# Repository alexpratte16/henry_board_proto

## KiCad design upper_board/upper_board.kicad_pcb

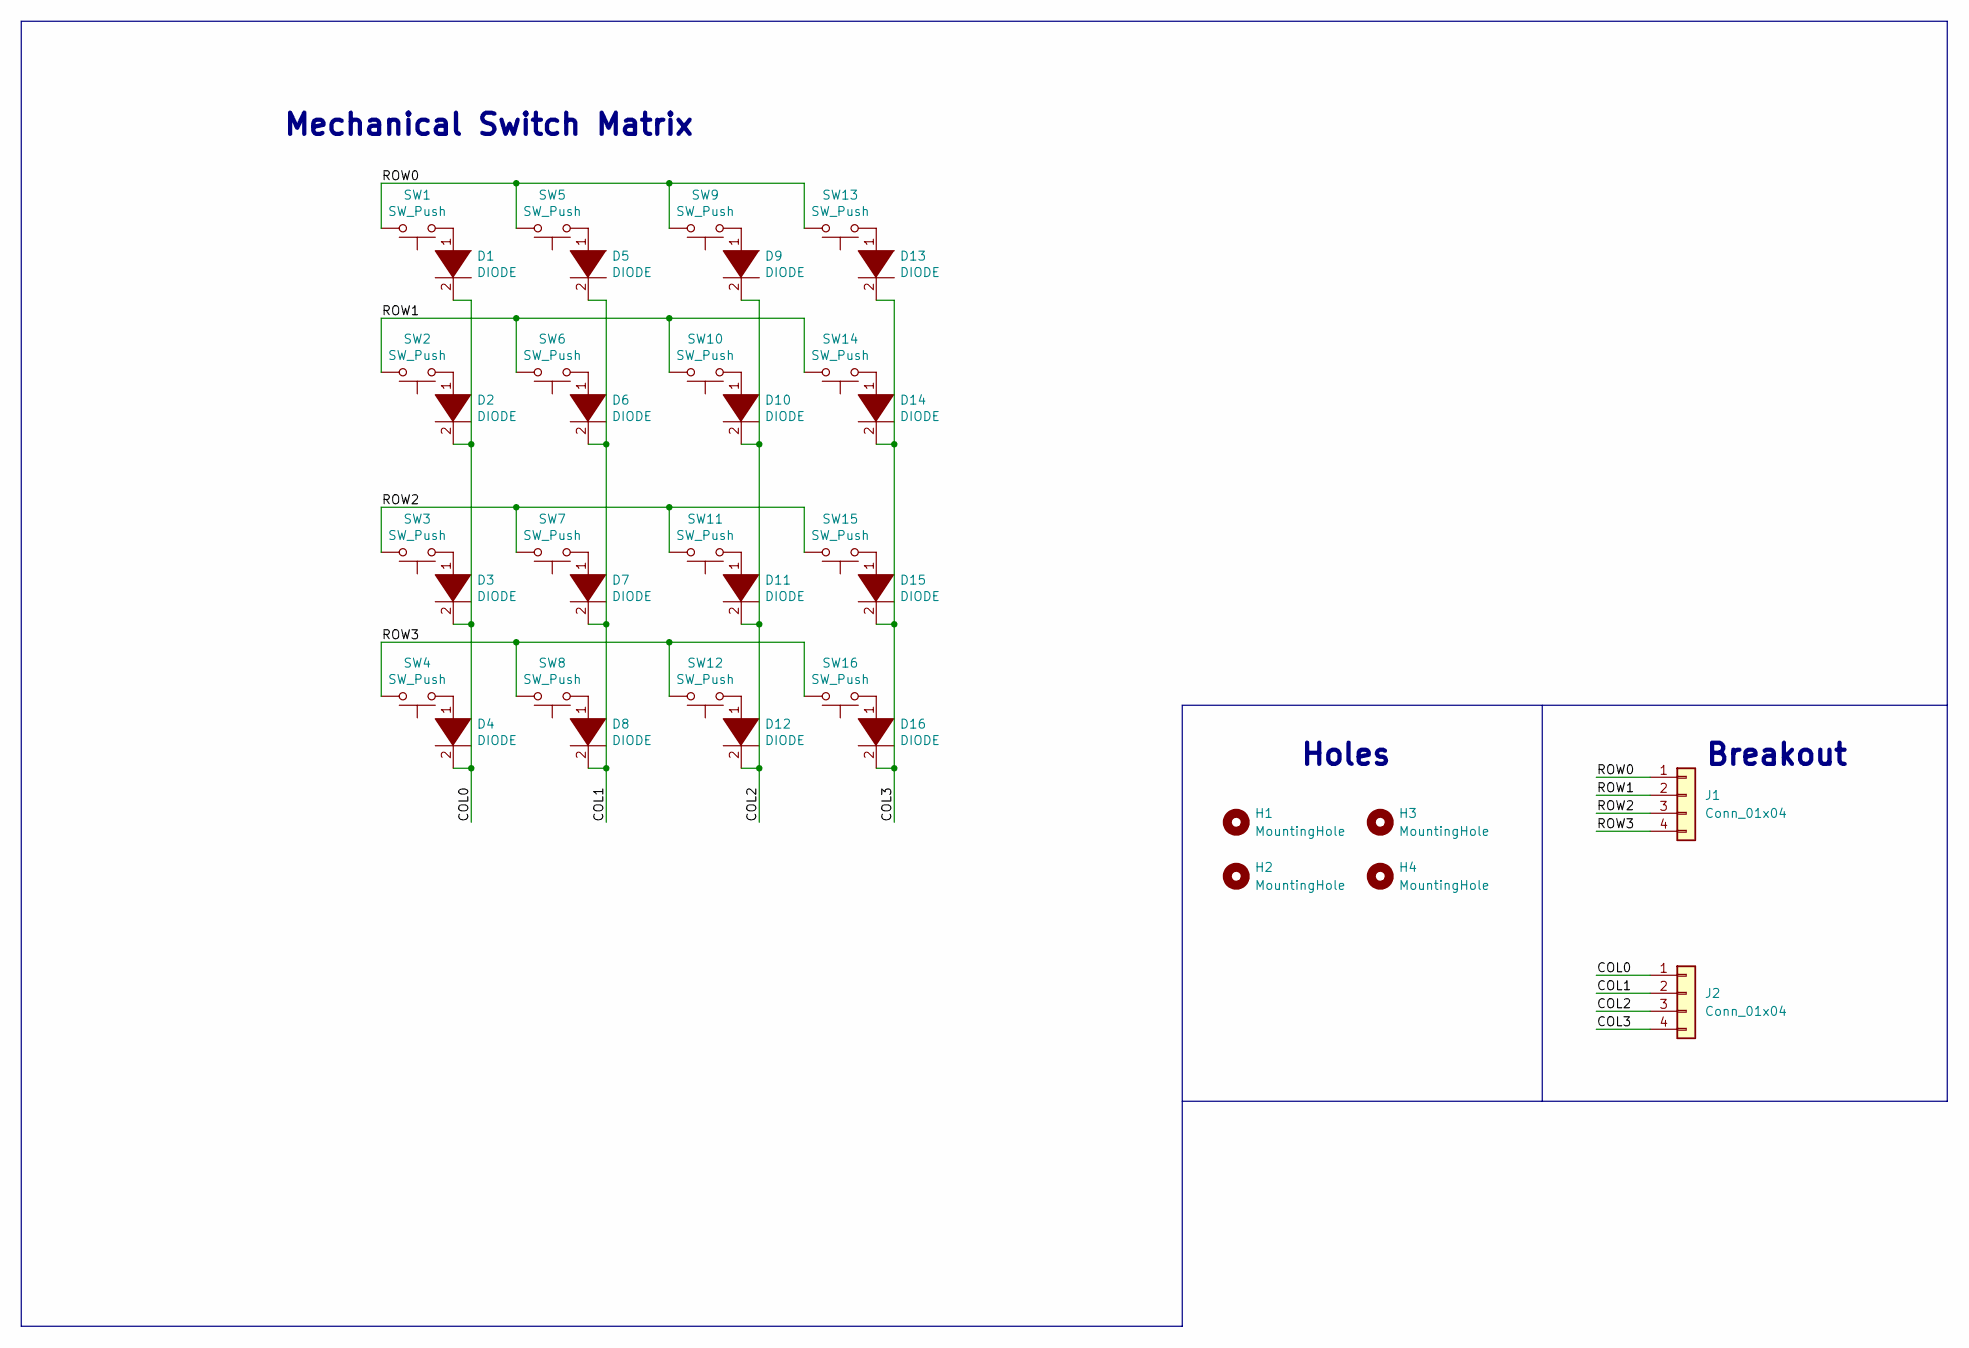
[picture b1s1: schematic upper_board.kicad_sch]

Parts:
D1, D2, D3, D4, D5, D6, D7, D8, D9, D10, D11, D12, D13, D14, D15, D16: DIODE; D_1206_3216Metric
H1, H2, H3, H4: MountingHole; MountingHole_2.5mm_Pad_Via
J1, J2: Conn_01x04; PinHeader_1x04_P2.54mm_Horizontal
SW1, SW2, SW3, SW4, SW5, SW6, SW7, SW8, SW9, SW10, SW11, SW12, SW13, SW14, SW15, SW16: SW_Push; SW_Cherry_MX_1.00u_PCB

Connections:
/COL0: D1.2 (A), D2.2 (A), D3.2 (A), D4.2 (A), J2.1
/COL1: D5.2 (A), D6.2 (A), D7.2 (A), D8.2 (A), J2.2
/COL2: D9.2 (A), D10.2 (A), D11.2 (A), D12.2 (A), J2.3
/COL3: D13.2 (A), D14.2 (A), D15.2 (A), D16.2 (A), J2.4
/ROW0: J1.1, SW1.2, SW5.2, SW9.2, SW13.2
/ROW1: J1.2, SW2.2, SW6.2, SW10.2, SW14.2
/ROW2: J1.3, SW3.2, SW7.2, SW11.2, SW15.2
/ROW3: J1.4, SW4.2, SW8.2, SW12.2, SW16.2
unnamed: D1.1 (K), SW1.1
unnamed: D2.1 (K), SW2.1
unnamed: D3.1 (K), SW3.1
unnamed: D4.1 (K), SW4.1
unnamed: D5.1 (K), SW5.1
unnamed: D6.1 (K), SW6.1
unnamed: D7.1 (K), SW7.1
unnamed: D8.1 (K), SW8.1
unnamed: D9.1 (K), SW9.1
unnamed: D10.1 (K), SW10.1
unnamed: D11.1 (K), SW11.1
unnamed: D12.1 (K), SW12.1
unnamed: D13.1 (K), SW13.1
unnamed: D14.1 (K), SW14.1
unnamed: D15.1 (K), SW15.1
unnamed: D16.1 (K), SW16.1

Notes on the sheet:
Holes
Mechanical Switch Matrix
Breakout

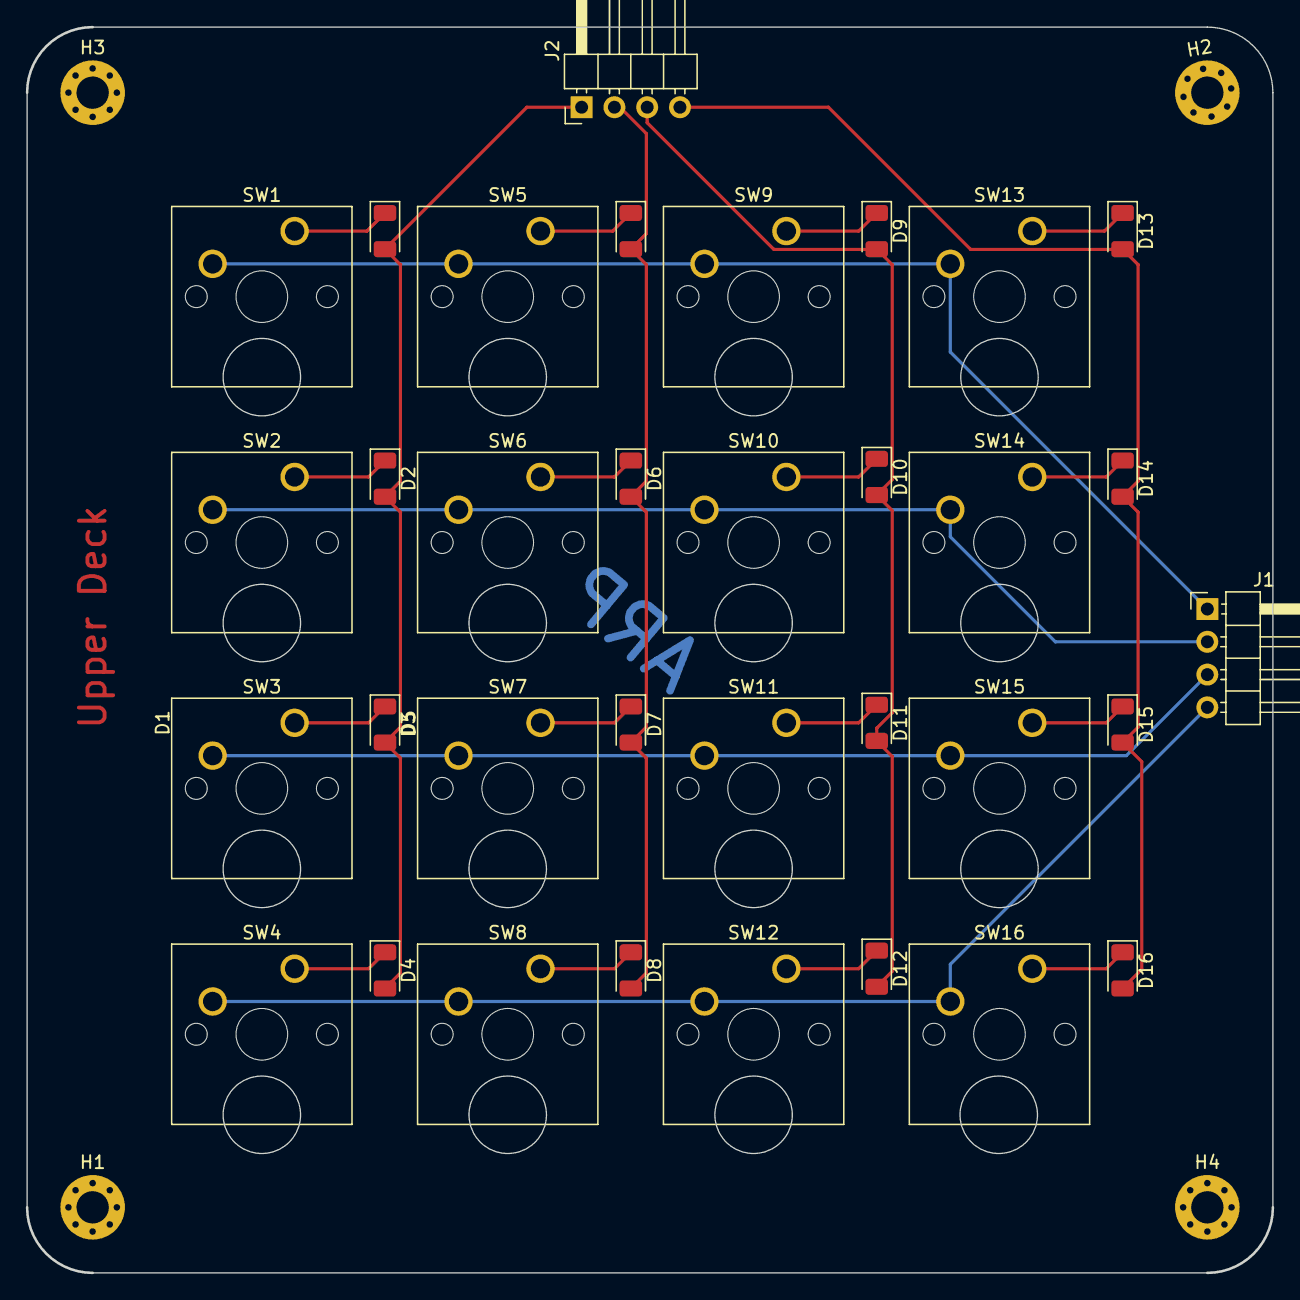
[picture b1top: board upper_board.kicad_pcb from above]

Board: 2 copper layers, 96.5 x 96.5 mm, 38 parts (0 on the bottom side), 24 nets.

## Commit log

2023-03-12 Uploading current state of boards
2023-03-12 lower board component placement
2023-03-12 Lower board routing
2023-03-25 Upgraded projects to KiCAD 7 Finished routing Added BOMs
